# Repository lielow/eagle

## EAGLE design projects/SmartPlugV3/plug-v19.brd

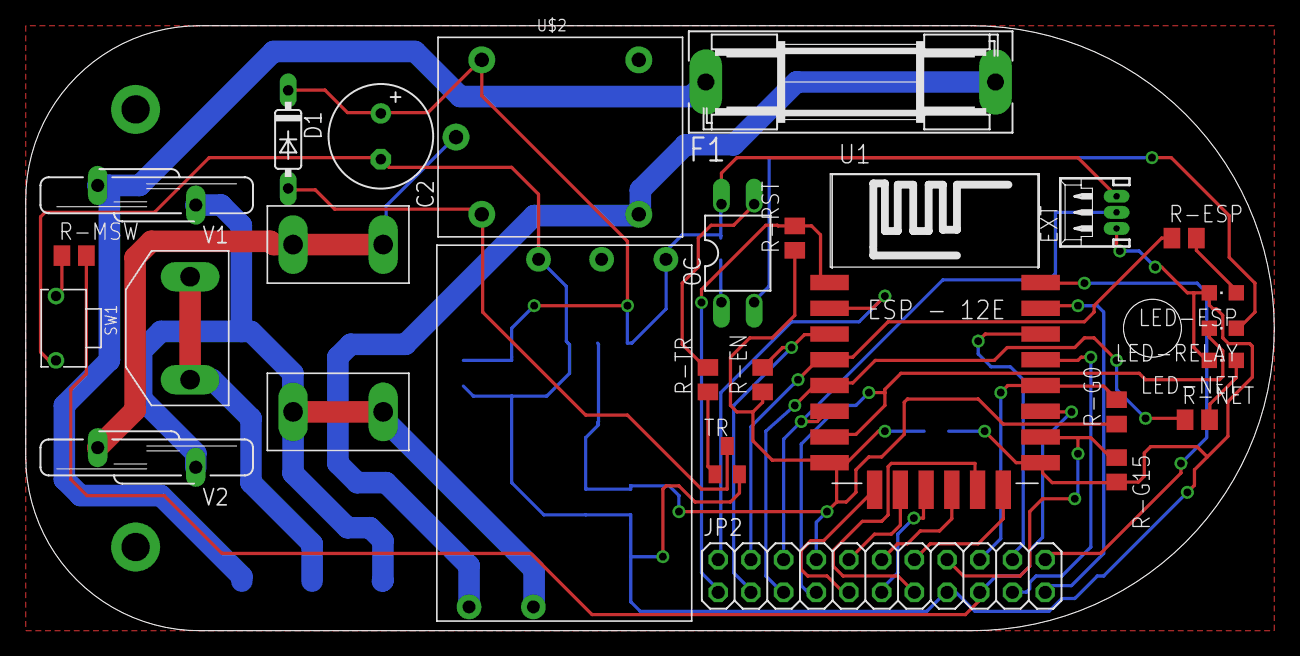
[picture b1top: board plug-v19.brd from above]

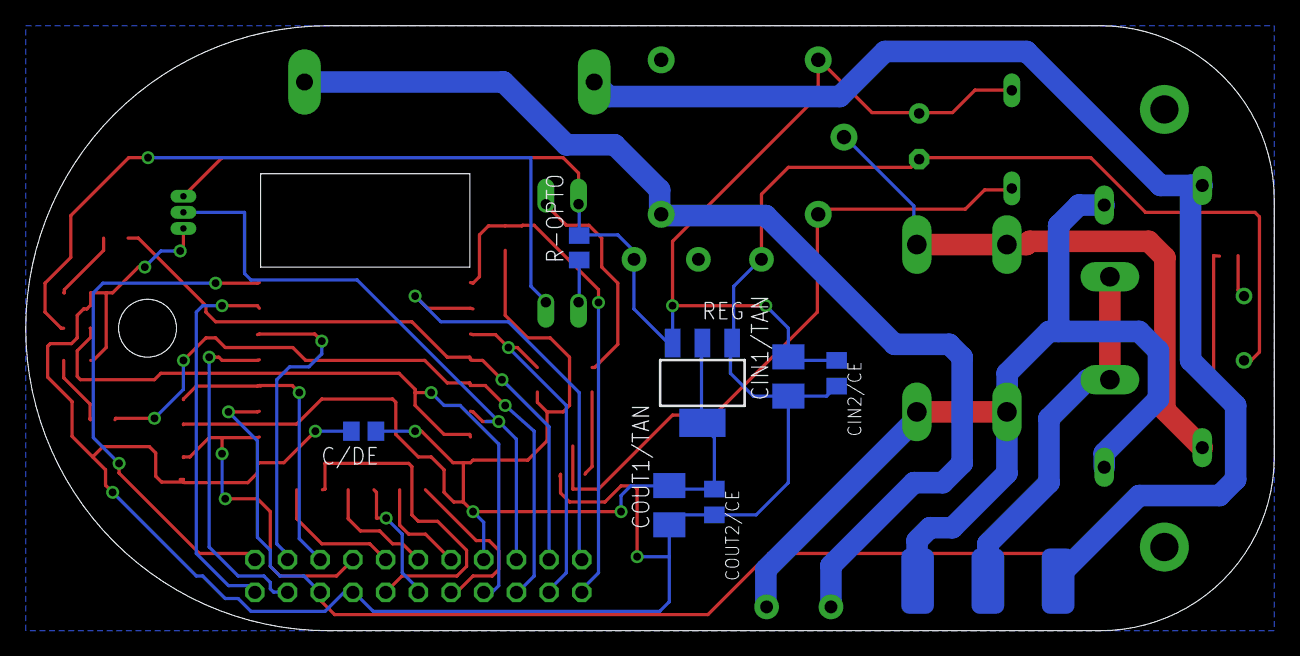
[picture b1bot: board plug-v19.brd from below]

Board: 2 copper layers, 97.0 x 47.0 mm, 33 parts (8 on the bottom side), 36 nets.

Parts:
C2: 470-1000uF; E3,5-8
C/DE: 0.1uF; C0805
CIN1/TAN: 22uF; B/3528-21R
CIN2/CE: 0.1uF; C0805K
COUT1/TAN: 22uF; B/3528-21R
COUT2/CE: 0.1uF; C0805K
D1: 1N4148; DO35-7
EXT: 53048-03
F1: FUSESH22,5; SH22,5
JP2: 2X11
LED-ESP: CHIPLED_0805
LED-NET: CHIPLED_0805
LED-RELAY: CHIPLED_0805
OC: PC817; DIL04
R-EN: 10k; M0805
R-ESP: 470; M0805
R-G0: 10k; M0805
R-G15: 1k; M0805
R-MSW: 470; M0805
R-NET: 470; M0805
R-OPTO: 1k; M0805
R-RST: 10k; M0805
R-TR: 510; M0805
REG: SOT-223
SW1: SW2-5.0-6.0X3.0X4.3MM
TR: BC817; SOT23-BEC
U1: ESP12E-SMD
U$2: RELAY-SONGLE
U$3: MALE-PLUG
U$4: POWERSUPPLY-5V-700MA
U$5: FEMALE-PLUG
V1, V2: S14K11

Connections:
3V3: C/DE.1, COUT1/TAN.+, COUT2/CE.1, JP2.8, R-EN.1, R-G0.1, R-RST.1, REG.2, REG.4, U1.VCC
+5V: C2.+, CIN1/TAN.+, CIN2/CE.1, D1.C, EXT.1, OC.4, R-OPTO.2, REG.3, U$2.V+, U$4.5V
ADC: JP2.2, U1.ADC
CS0: JP2.9, U1.CS0
EN: JP2.3, R-EN.2, U1.CH_PD
G: U$3.G, U$5.G1, U$5.G2
G-00: JP2.18, R-G0.2, U1.GPIO0
G-02: JP2.17, R-MSW.2, U1.GPIO2
G-04: JP2.19, U1.GPIO4
G-05: JP2.20, U1.GPIO5
G-09: JP2.11, U1.GPIO9
G-10: JP2.12, U1.GPIO10
G-12: EXT.2, JP2.6, U1.GPIO12
G-13: JP2.7, LED-RELAY.C, U1.GPIO13
G-14: JP2.5, R-NET.1, U1.GPIO14
G-15: JP2.16, R-G15.1, U1.GPIO15
G-16: JP2.4, R-ESP.1, U1.GPIO16
GND: C2.-, C/DE.2, CIN1/TAN.-, CIN2/CE.2, COUT1/TAN.-, COUT2/CE.2, EXT.3, JP2.15, LED-ESP.C, LED-NET.C, R-G15.2, REG.1, SW1.2, TR.E, U1.GND, U$4.GND
LINE: F1.1, U$3.L, V1.2
MISO: JP2.10, U1.MISO
MOSI: JP2.13, U1.MOSI
N: U$3.N, U$4.AC2, U$5.N1, U$5.N2, V1.1, V2.1
unnamed: OC.3, R-TR.2
unnamed: R-TR.1, TR.B
unnamed: LED-ESP.A, R-ESP.2
unnamed: OC.1, R-OPTO.1
unnamed: LED-NET.A, R-NET.2
unnamed: D1.A, TR.C, U$2.V-
unnamed: LED-RELAY.A, OC.2
unnamed: R-MSW.1, SW1.1
RELAY-COM: U$2.COM, U$5.L1, U$5.L2, V2.2
RELAY-NO: F1.2, U$2.NO, U$4.AC1
RST: JP2.1, R-RST.2, U1.RESET
RX: JP2.21, U1.RXD0
SCLK: JP2.14, U1.SCLK
TX: JP2.22, U1.TXD0

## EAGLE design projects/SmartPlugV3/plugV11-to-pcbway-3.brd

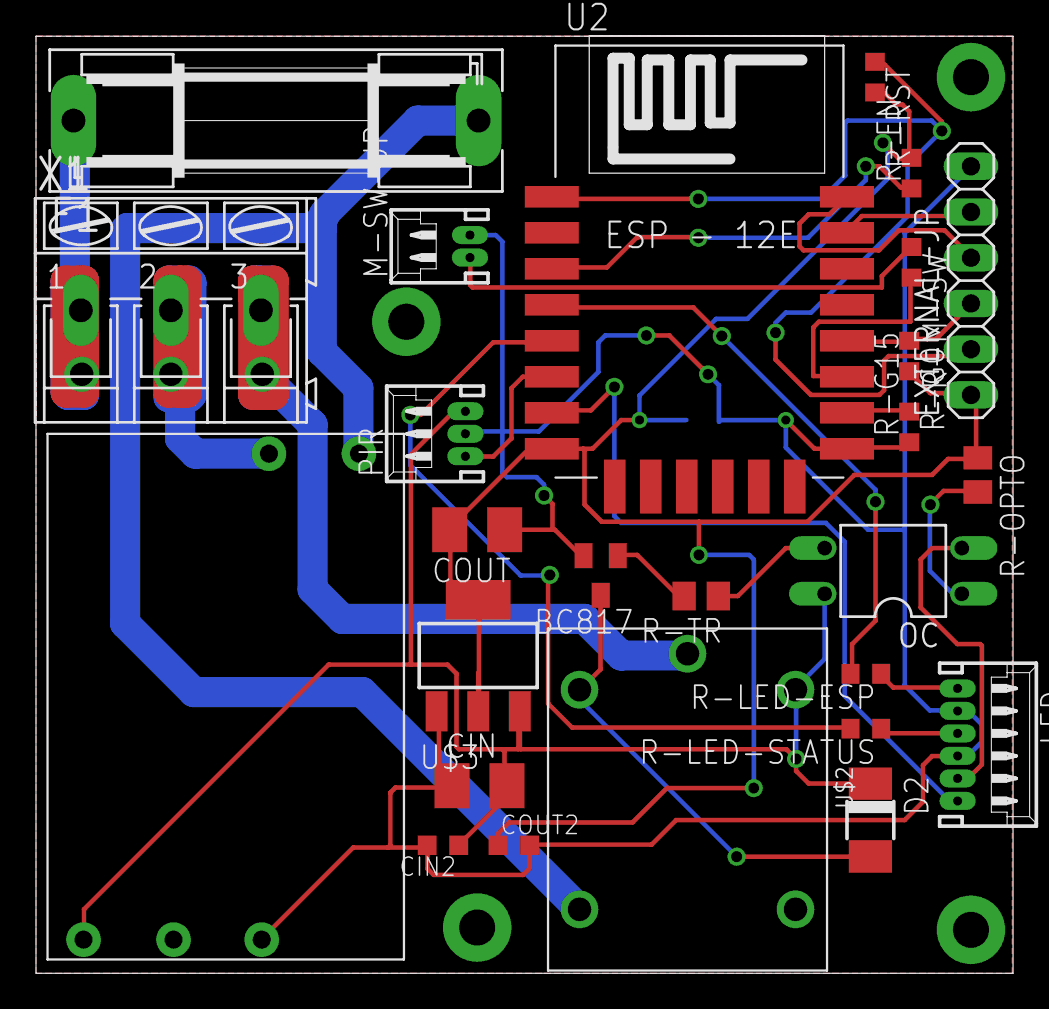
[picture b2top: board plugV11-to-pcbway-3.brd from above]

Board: 2 copper layers, 54.3 x 52.1 mm, 27 parts (1 on the bottom side), 26 nets.

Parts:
BC817: SOT23-BEC
C/DE: 0.1uF; C0805
CIN: 22uF/Tan; B/3528-21R
CIN2: 0.1uF/ce; C0603K
COUT: 22uF/Tan; B/3528-21R
COUT2: 0.1uF/ce; C0603K
D2: DO-214AC
EXTERNAL-JP: Programming; 1X06
F1: FUSESH22,5; SH22,5
LED: 53048-06
M-SW-JP: 53048-02
OC: PC817; DIL04
PIR: 53048-03
R-EN: 10k; R0603
R-G0: 10k; R0603
R-G15: 1k; R0603
R-LED-ESP: 470; R0603
R-LED-STATUS: 470; R0603
R-M-SW: 470; R0603
R-OPTO: 1k; M0805
R-RST: 10k; R0603
R-TR: 510; M0805
U2: ESP12E-SMD
U$2: RELAY-SONGLE
U$3: AMS1117-3.3; SOT-223
U$4: POWERSUPPLY-5V-700MA
X1: AK300/3

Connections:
3V3: C/DE.1, COUT.+, COUT2.1, EXTERNAL-JP.1, R-EN.2, R-G0.2, R-OPTO.1, R-RST.2, U2.VCC, U$3.2, U$3.4
+5V: CIN.+, CIN2.1, D2.C, OC.4, PIR.1, U$2.V+, U$3.3, U$4.5V
COM: U$2.COM, X1.3
EN: R-EN.1, U2.CH_PD
G-00: EXTERNAL-JP.3, R-G0.1, U2.GPIO0
G-12: PIR.3, U2.GPIO12
G-13: LED.1, U2.GPIO13
G-15: R-G15.2, U2.GPIO15
GND: BC817.E, C/DE.2, CIN.-, CIN2.2, COUT.-, COUT2.2, EXTERNAL-JP.6, LED.3, LED.5, M-SW-JP.1, PIR.2, R-G15.1, U2.GND, U$3.1, U$4.GND
LED-ESP+: LED.6, R-LED-ESP.1
LED-RELAY+: LED.2, OC.2
LED-STATUS+: LED.4, R-LED-STATUS.1
LINE: F1.1, X1.1
M-SW+: M-SW-JP.2, R-M-SW.1
N: U$4.AC2, X1.2
unnamed: OC.3, R-TR.1
unnamed: BC817.B, R-TR.2
unnamed: R-LED-ESP.2, U2.GPIO16
unnamed: R-M-SW.2, U2.GPIO2
unnamed: R-LED-STATUS.2, U2.GPIO14
unnamed: OC.1, R-OPTO.2
unnamed: BC817.C, D2.A, U$2.V-
RELAY-NO: F1.2, U$2.NO, U$4.AC1
RST: EXTERNAL-JP.2, R-RST.1, U2.RESET
RX: EXTERNAL-JP.5, U2.RXD0
TX: EXTERNAL-JP.4, U2.TXD0

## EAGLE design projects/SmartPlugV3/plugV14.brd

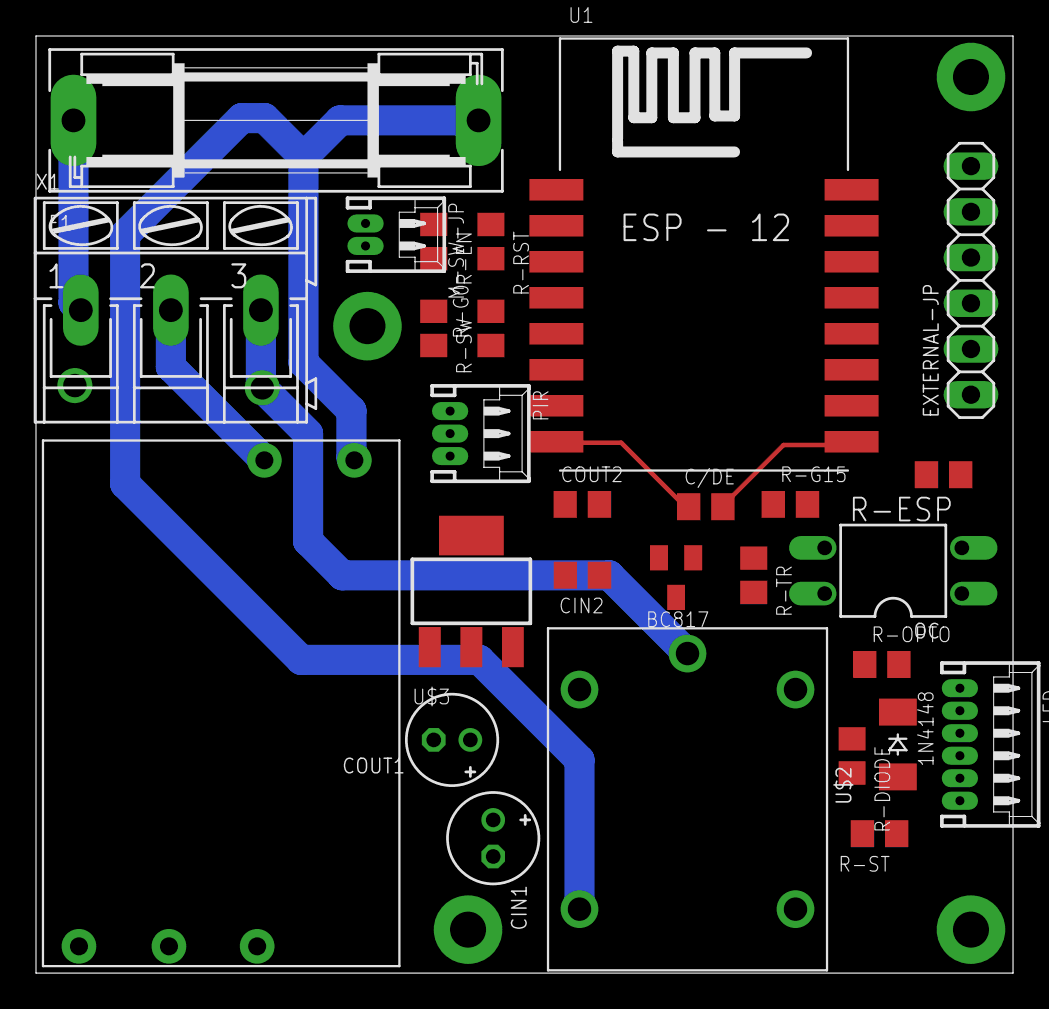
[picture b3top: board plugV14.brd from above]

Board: 2 copper layers, 54.3 x 52.1 mm, 28 parts (0 on the bottom side), 27 nets.

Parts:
1N4148: sod-123; SOD-123_MINI-SMA
BC817: SOT23-BEC
C/DE: 0.1uF/Ce; C0805
CIN1: 47uF/Ele; E2-5
CIN2: 0.1uF/Ce; C0805
COUT1: 47uF/Ele; E2-5
COUT2: 0.1uF/Ce; C0805
EXTERNAL-JP: Programming; 1X06
F1: FUSESH22,5; SH22,5
LED: 53048-06
M-SW-JP: 53048-02
OC: PC817; DIL04
PIR: 53048-03
R-DIODE: 33; R0805
R-EN: 10k; R0805
R-ESP: 470; R0805
R-G0, R-G15: 10k; R0805
R-OPTO: 1k; R0805
R-RST: 10k; R0805
R-ST: 470; R0805
R-SW: 470; R0805
R-TR: 510; R0805
U1: ESP12-SMD
U$2: RELAY-SONGLE
U$3: AMS1117-3.3; SOT-223
U$4: POWERSUPPLY-5V-700MA
X1: AK300/3

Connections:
3V3: C/DE.1, COUT1.+, COUT2.1, EXTERNAL-JP.1, R-EN.2, R-G0.2, R-RST.2, U1.VCC, U$3.2, U$3.4
+5V: 1N4148.C, CIN1.+, CIN2.1, OC.4, PIR.1, R-OPTO.1, U$2.V+, U$3.3, U$4.5V
COM: U$2.COM, X1.3
EN: R-EN.1, U1.CH_PD
G-00: EXTERNAL-JP.3, R-G0.1, U1.GPIO0
G-12: PIR.3, U1.GPIO12
G-13: LED.1, U1.GPIO13
G-15: R-G15.2, U1.GPIO15
GND: BC817.E, C/DE.2, CIN1.-, CIN2.2, COUT1.-, COUT2.2, EXTERNAL-JP.6, LED.3, LED.5, M-SW-JP.1, PIR.2, R-G15.1, U1.GND, U$3.1, U$4.GND
LED-ESP+: LED.6, R-ESP.1
LED-RELAY+: LED.2, OC.2
LED-STATUS+: LED.4, R-ST.1
LINE: F1.1, X1.1
M-SW+: M-SW-JP.2, R-SW.1
N: U$4.AC2, X1.2
unnamed: OC.3, R-TR.1
unnamed: BC817.B, R-TR.2
unnamed: R-ESP.2, U1.GPIO16
unnamed: R-SW.2, U1.GPIO2
unnamed: R-ST.2, U1.GPIO14
unnamed: OC.1, R-OPTO.2
unnamed: 1N4148.A, R-DIODE.2
unnamed: BC817.C, R-DIODE.1, U$2.V-
RELAY-NO: F1.2, U$2.NO, U$4.AC1
RST: EXTERNAL-JP.2, R-RST.1, U1.RESET
RX: EXTERNAL-JP.5, U1.RXD0
TX: EXTERNAL-JP.4, U1.TXD0

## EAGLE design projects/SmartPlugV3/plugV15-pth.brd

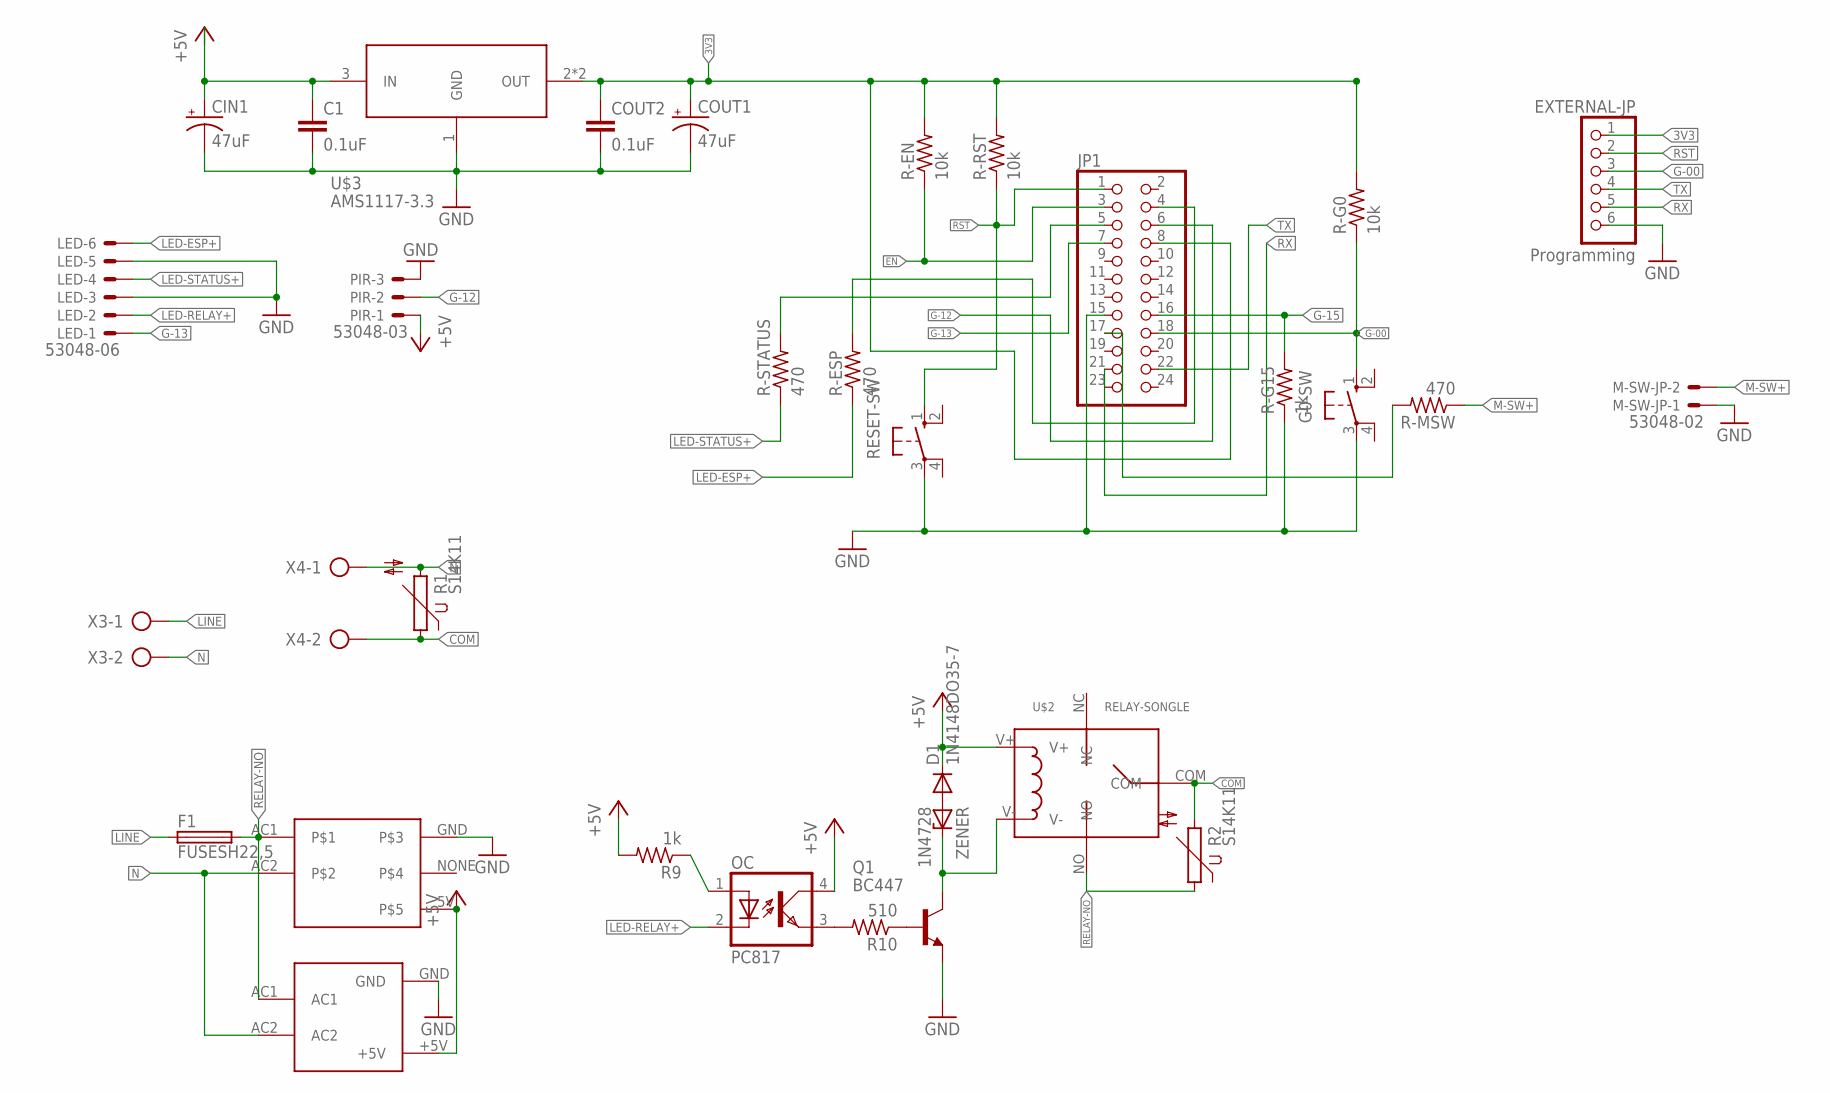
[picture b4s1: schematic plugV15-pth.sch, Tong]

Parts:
C1: 0.1uF; C050-024X044
CIN1: 47uF; E2,5-5
COUT1: 47uF; E2,5-5
COUT2: 0.1uF; C050-024X044
D1: 1N4148DO35-7; DO35-7
EXTERNAL-JP: Programming; 1X06
F1: FUSESH22,5; SH22,5
G0-SW: 10-XX; B3F-10XX
JP1: PINHD-2X12; 2X12
LED: 53048-06
M-SW-JP: 53048-02
OC: PC817; DIL04
PIR: 53048-03
Q1: BC447; TO92-EBC
R1, R2: S14K11
R9: 1k; 0207/10
R10: 510; 0207/10
R-EN: 10k; 0207/10
R-ESP: 470; 0207/10
R-G0: 10k; 0207/10
R-G15: 1k; 0207/10
R-MSW: 470; 0207/10
R-RST: 10k; 0207/10
R-STATUS: 470; 0207/10
RESET-SW: 10-XX; B3F-10XX
U$1: HLK-PM01
U$2: RELAY-SONGLE
U$3: AMS1117-3.3; SOT-223
U$4: POWERSUPPLY-5V-700MA
X3, X4: AK300/2
ZENER: 1N4728; DO41Z10

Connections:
3V3: COUT1.+, COUT2.1, EXTERNAL-JP.1, JP1.8, R-EN.2, R-G0.2, R-RST.2, U$3.2 (OUT), U$3.4 (OUT)
+5V: C1.1, CIN1.+, D1.C, OC.4 (COL), PIR.1, R9.2, U$1.+5V, U$2.V+, U$3.3 (IN), U$4.5V
COM: R1.1, R2.2, U$2.COM, X4.2
EN: JP1.3, R-EN.1
G-00: EXTERNAL-JP.3, G0-SW.1 (S), JP1.18, R-G0.1
G-12: JP1.6, PIR.2
G-13: JP1.7, LED.1
G-15: JP1.16, R-G15.2
GND: C1.2, CIN1.-, COUT1.-, COUT2.2, EXTERNAL-JP.6, G0-SW.3, JP1.15, LED.3, LED.5, M-SW-JP.1, PIR.3, Q1.E, R-G15.1, RESET-SW.3, U$1.GND, U$3.1 (GND), U$4.GND
LED-ESP+: LED.6, R-ESP.1
LED-RELAY+: LED.2, OC.2 (C)
LED-STATUS+: LED.4, R-STATUS.1
LINE: F1.1, X3.1
M-SW+: M-SW-JP.2, R-MSW.1
N: R1.2, U$1.AC2, U$4.AC2, X3.2, X4.1
unnamed: OC.3 (EMIT), R10.2
unnamed: Q1.B, R10.1
unnamed: JP1.4, R-ESP.2
unnamed: JP1.17, R-MSW.2
unnamed: JP1.5, R-STATUS.2
unnamed: OC.1 (A), R9.1
unnamed: D1.A, ZENER.A
unnamed: Q1.C, U$2.V-, ZENER.C
RELAY-NO: F1.2, R2.1, U$1.AC1, U$2.NO, U$4.AC1
RST: EXTERNAL-JP.2, JP1.1, R-RST.1, RESET-SW.1 (S)
RX: EXTERNAL-JP.5, JP1.21
TX: EXTERNAL-JP.4, JP1.22

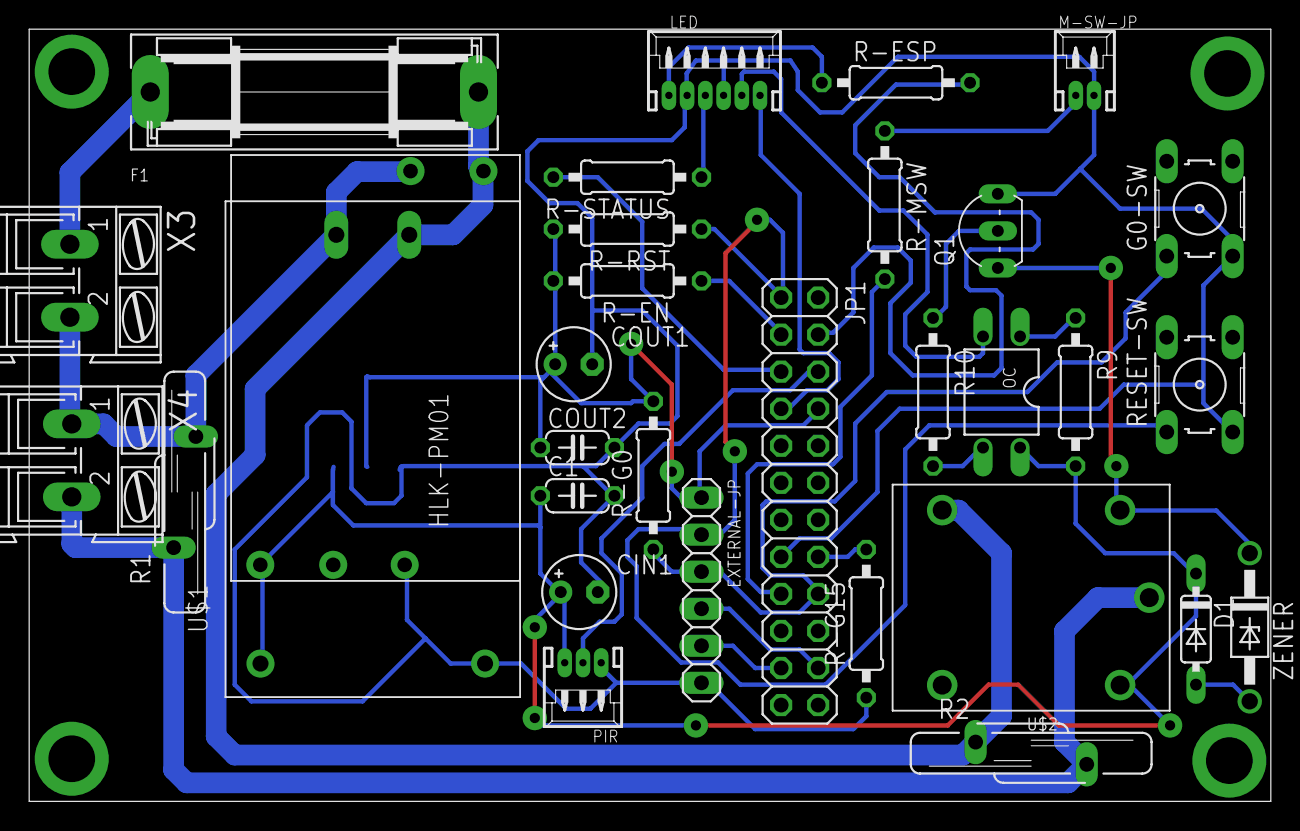
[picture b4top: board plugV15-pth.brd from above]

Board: 2 copper layers, 85.1 x 52.9 mm, 33 parts (1 on the bottom side), 27 nets.

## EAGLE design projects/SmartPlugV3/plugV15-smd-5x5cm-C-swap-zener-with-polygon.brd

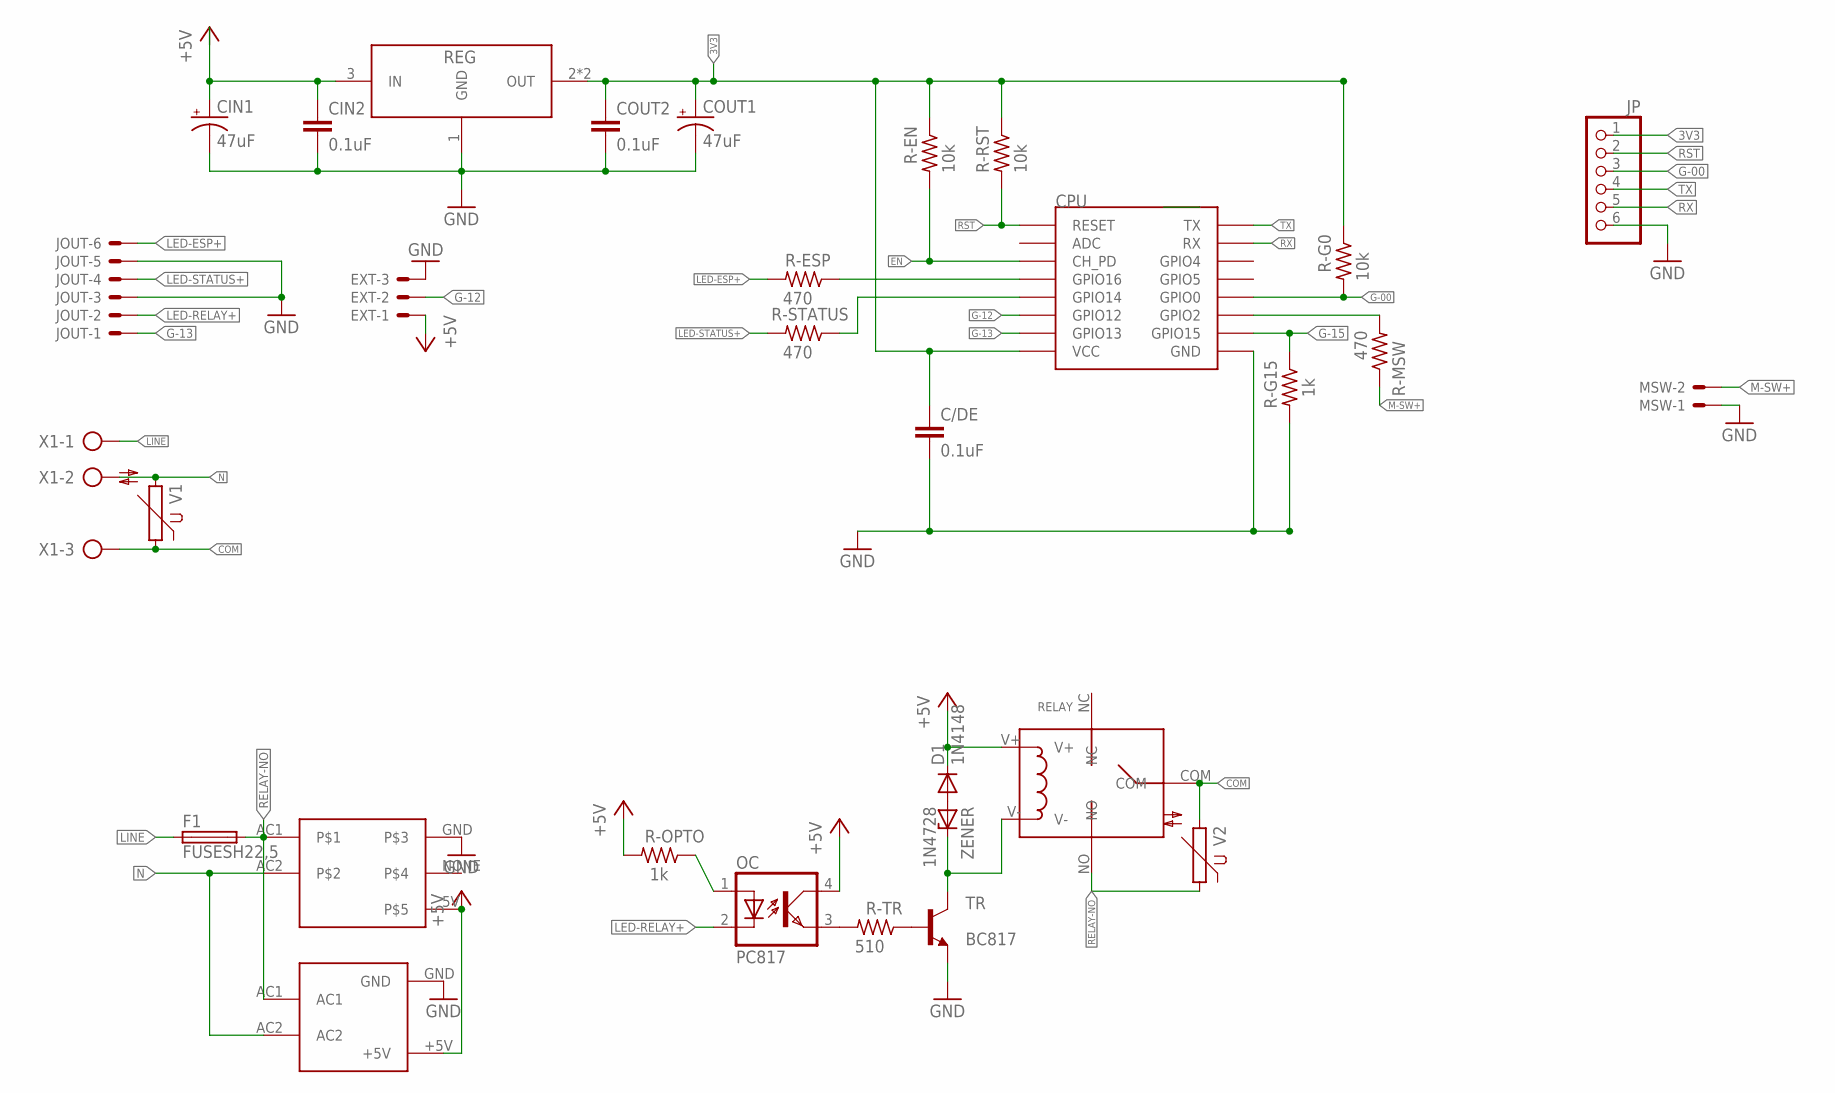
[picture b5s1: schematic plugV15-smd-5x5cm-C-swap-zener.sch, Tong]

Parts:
C/DE: 0.1uF; C0805
CIN1: 47uF; E2,5-5
CIN2: 0.1uF; C0805
COUT1: 47uF; E2,5-5
COUT2: 0.1uF; C0805
CPU: ESP12SMD; ESP12-SMD
D1: 1N4148; DO35-7
EXT: 53048-03
F1: FUSESH22,5; SH22,5
HLK: HLK-PM01
JOUT: 53048-06
JP: PINHD-1X6; 1X06
MSW: 53048-02
OC: PC817; DIL04
R-EN: 10k; M0805
R-ESP: 470; M0805
R-G0: 10k; M0805
R-G15: 1k; M0805
R-MSW: 470; M0805
R-OPTO: 1k; M0805
R-RST: 10k; M0805
R-STATUS: 470; M0805
R-TR: 510; M0805
REG: AMS1117-3.3; SOT-223
RELAY: RELAY-SONGLE
TR: BC817; SOT23-BEC
U$4: POWERSUPPLY-5V-700MA
V1, V2: S14K11
X1: AK300/3
ZENER: 1N4728; DO41Z10

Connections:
3V3: C/DE.1, COUT1.+, COUT2.1, CPU.VCC, JP.1, R-EN.1, R-G0.1, R-RST.1, REG.2 (OUT), REG.4 (OUT)
+5V: CIN1.+, CIN2.1, D1.C, EXT.1, HLK.+5V, OC.4 (COL), R-OPTO.2, REG.3 (IN), RELAY.V+, U$4.5V
COM: RELAY.COM, V1.1, V2.2, X1.3
EN: CPU.CH_PD, R-EN.2
G-00: CPU.GPIO0, JP.3, R-G0.2
G-12: CPU.GPIO12, EXT.2
G-13: CPU.GPIO13, JOUT.1
G-15: CPU.GPIO15, R-G15.1
GND: C/DE.2, CIN1.-, CIN2.2, COUT1.-, COUT2.2, CPU.GND, EXT.3, HLK.GND, JOUT.3, JOUT.5, JP.6, MSW.1, R-G15.2, REG.1 (GND), TR.E, U$4.GND
LED-ESP+: JOUT.6, R-ESP.2
LED-RELAY+: JOUT.2, OC.2 (C)
LED-STATUS+: JOUT.4, R-STATUS.2
LINE: F1.1, X1.1
M-SW+: MSW.2, R-MSW.1
N: HLK.AC2, U$4.AC2, V1.2, X1.2
unnamed: OC.3 (EMIT), R-TR.2
unnamed: R-TR.1, TR.B
unnamed: CPU.GPIO2, R-MSW.2
unnamed: CPU.GPIO14, R-STATUS.1
unnamed: OC.1 (A), R-OPTO.1
unnamed: D1.A, ZENER.A
unnamed: RELAY.V-, TR.C, ZENER.C
unnamed: CPU.GPIO16, R-ESP.1
RELAY-NO: F1.2, HLK.AC1, RELAY.NO, U$4.AC1, V2.1
RST: CPU.RESET, JP.2, R-RST.2
RX: CPU.RXD0 (RX), JP.5
TX: CPU.TXD0 (TX), JP.4

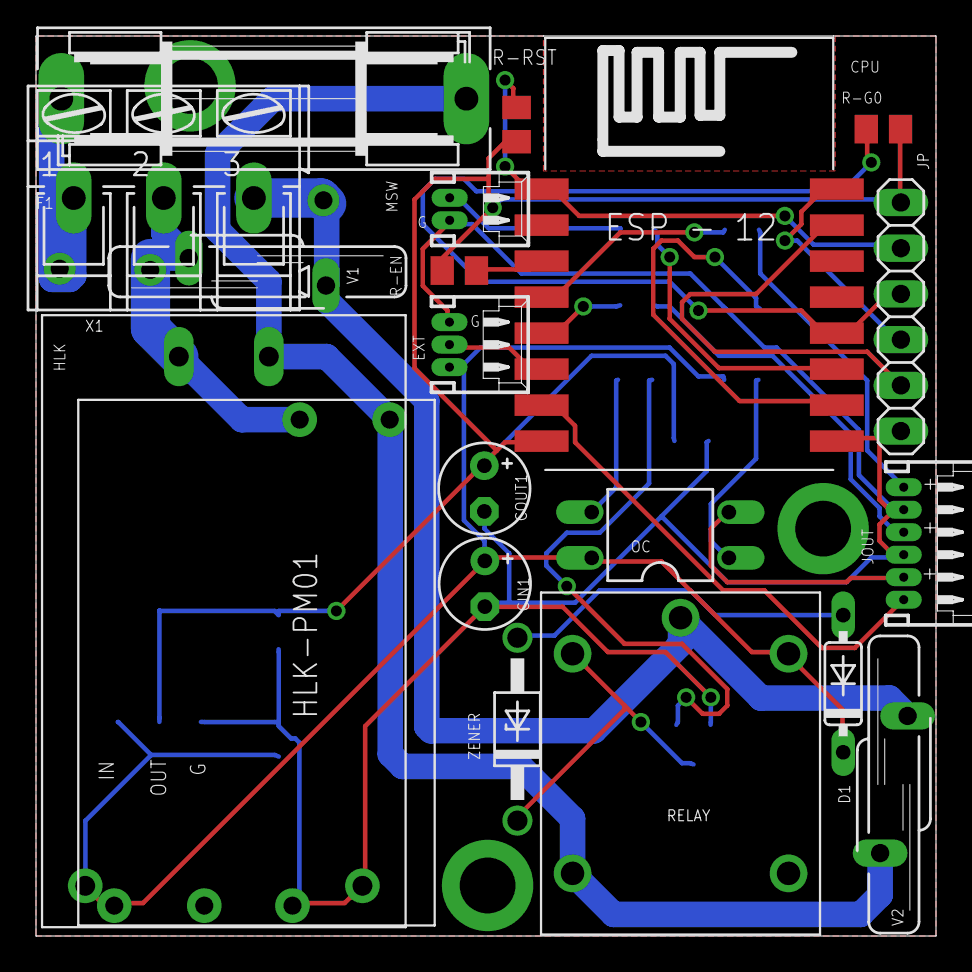
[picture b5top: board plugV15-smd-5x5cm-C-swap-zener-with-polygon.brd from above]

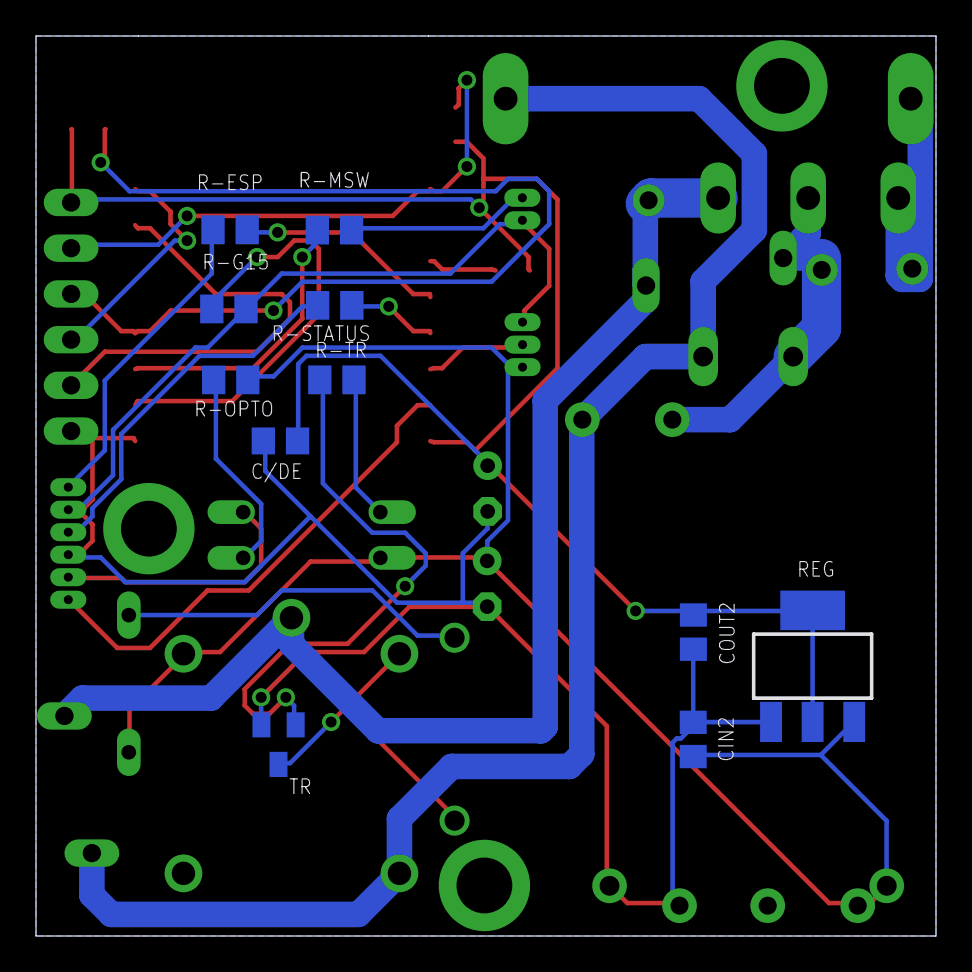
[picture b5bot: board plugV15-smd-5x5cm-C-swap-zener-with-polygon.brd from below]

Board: 2 copper layers, 50.0 x 50.0 mm, 31 parts (11 on the bottom side), 27 nets.

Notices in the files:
parts and their libraries:
SparkFun-Aesthetics: Licensing: Creative Commons ShareAlike 4.0 International - https://creativecommons.org/licenses/by-sa/4.0
